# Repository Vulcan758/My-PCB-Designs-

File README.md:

# My-PCB-Designs-
all the designs I have so far

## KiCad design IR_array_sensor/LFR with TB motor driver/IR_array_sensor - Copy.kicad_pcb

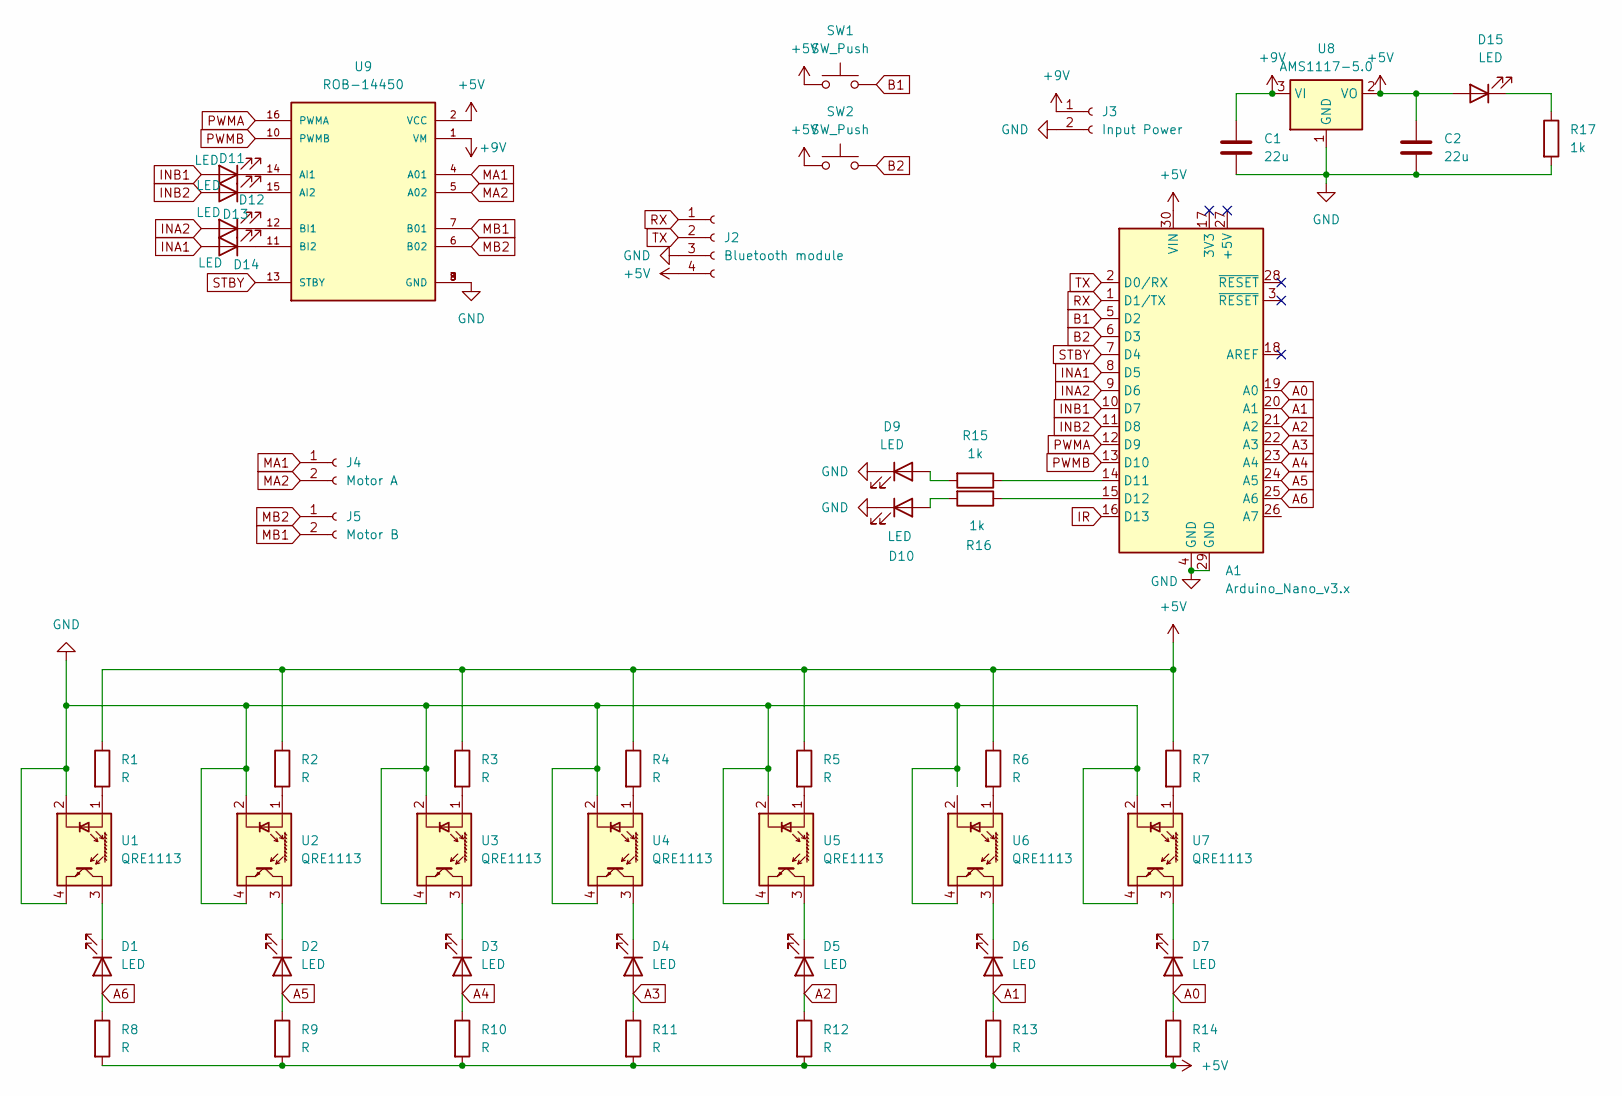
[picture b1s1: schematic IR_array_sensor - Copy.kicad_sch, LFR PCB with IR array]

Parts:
A1: Arduino_Nano_v3.x; Arduino_Nano
C1: 22u; CP_Radial_D5.0mm_P2.50mm
C2: 22u; CP_Radial_D5.0mm_P2.00mm
D1, D2, D3, D4, D5, D6, D7: LED; LED_D5.0mm
D9, D10, D11, D12, D13, D14, D15: LED; LED_D3.0mm
J2: Bluetooth module; PinSocket_1x04_P2.54mm_Vertical
J3: Input Power; BarrelJack_GCT_DCJ200-10-A_Horizontal
J4: Motor A; JST_XH_S2B-XH-A-1_1x02_P2.50mm_Horizontal
J5: Motor B; JST_XH_S2B-XH-A-1_1x02_P2.50mm_Horizontal
R1, R2, R3, R4, R5, R6, R7, R8, R9, R10, R11, R12, R13, R14: R; R_Axial_DIN0204_L3.6mm_D1.6mm_P5.08mm_Horizontal
R15, R16, R17: 1k; R_Axial_DIN0204_L3.6mm_D1.6mm_P5.08mm_Horizontal
SW1, SW2: SW_Push; SW_PUSH_6mm_H4.3mm
U1, U2, U3, U4, U5, U6, U7: QRE1113; OnSemi_CASE100AQ
U8: AMS1117-5.0; SOT-223-3_TabPin2
U9: ROB-14450; MODULE_ROB-14450; PARTREV 11-13-17

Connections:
+5V: A1.30 (VIN), C2.1, D15.2 (A), J2.4, R1.1, R2.1, R3.1, R4.1, R5.1, R6.1, R7.1, R8.2, R9.2, R10.2, R11.2, R12.2, R13.2, R14.2, SW1.1, SW2.1, U8.2 (VO), U9.2 (VCC)
+9V: C1.1, J3.1, U8.3 (VI), U9.1 (VM)
A0: A1.19 (A0), D7.2 (A), R14.1
A1: A1.20 (A1), D6.2 (A), R13.1
A2: A1.21 (A2), D5.2 (A), R12.1
A3: A1.22 (A3), D4.2 (A), R11.1
A4: A1.23 (A4), D3.2 (A), R10.1
A5: A1.24 (A5), D2.2 (A), R9.1
A6: A1.25 (A6), D1.2 (A), R8.1
B1: A1.5 (D2), SW1.2
B2: A1.6 (D3), SW2.2
GND: A1.4 (GND), A1.29 (GND), C1.2, C2.2, D9.1 (K), D10.1 (K), J2.3, J3.2, R17.2, U1.2 (K), U1.4, U2.2 (K), U2.4, U3.2 (K), U3.4, U4.2 (K), U4.4, U5.2 (K), U5.4, U6.4, U7.2 (K), U7.4, U8.1 (GND), U9.3 (GND), U9.8 (GND), U9.9 (GND)
INA1: A1.8 (D5), D14.2 (A)
INA2: A1.9 (D6), D13.2 (A)
INB1: A1.10 (D7), D11.2 (A)
INB2: A1.11 (D8), D12.2 (A)
IR: A1.16 (D13)
MA1: J4.1, U9.4 (A01)
MA2: J4.2, U9.5 (A02)
MB1: J5.2, U9.7 (B01)
MB2: J5.1, U9.6 (B02)
unnamed: A1.14 (D11), R15.1
unnamed: A1.15 (D12), R16.1
unnamed: D1.1 (K), U1.3
unnamed: D2.1 (K), U2.3
unnamed: D3.1 (K), U3.3
unnamed: D4.1 (K), U4.3
unnamed: D5.1 (K), U5.3
unnamed: D6.1 (K), U6.3
unnamed: D7.1 (K), U7.3
unnamed: D9.2 (A), R15.2
unnamed: D10.2 (A), R16.2
unnamed: D11.1 (K), U9.14 (AI1)
unnamed: D12.1 (K), U9.15 (AI2)
unnamed: D13.1 (K), U9.12 (BI1)
unnamed: D14.1 (K), U9.11 (BI2)
unnamed: D15.1 (K), R17.1
unnamed: R1.2, U1.1 (A)
unnamed: R2.2, U2.1 (A)
unnamed: R3.2, U3.1 (A)
unnamed: R4.2, U4.1 (A)
unnamed: R5.2, U5.1 (A)
unnamed: R6.2, U6.1 (A)
unnamed: R7.2, U7.1 (A)
PWMA: A1.12 (D9), U9.16 (PWMA)
PWMB: A1.13 (D10), U9.10 (PWMB)
RX: A1.1 (D1/TX), J2.1
STBY: A1.7 (D4), U9.13 (STBY)
TX: A1.2 (D0/RX), J2.2

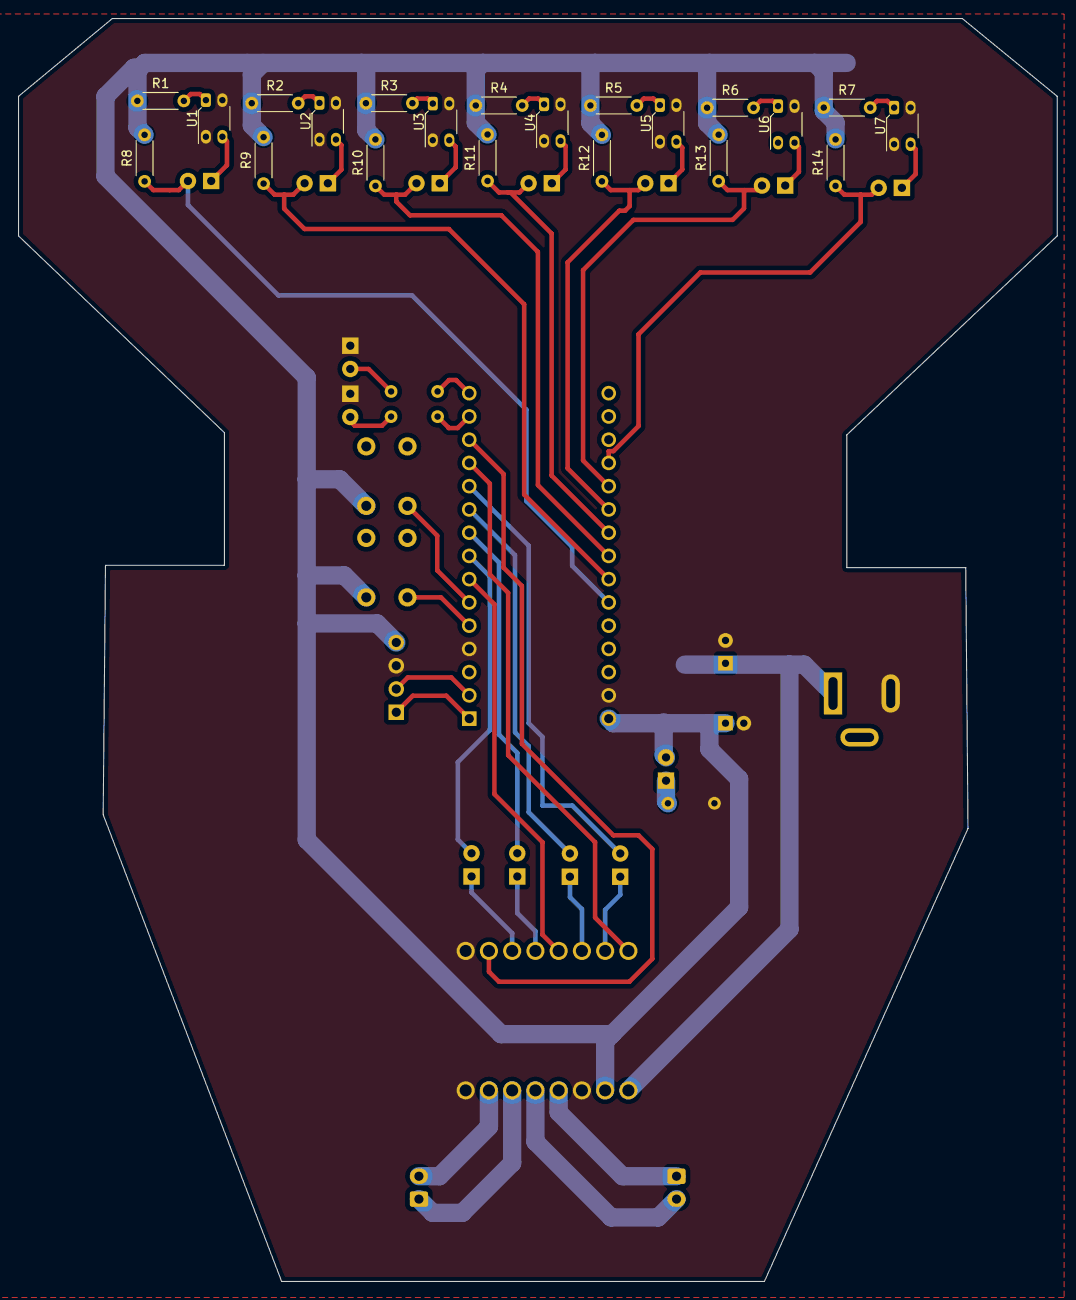
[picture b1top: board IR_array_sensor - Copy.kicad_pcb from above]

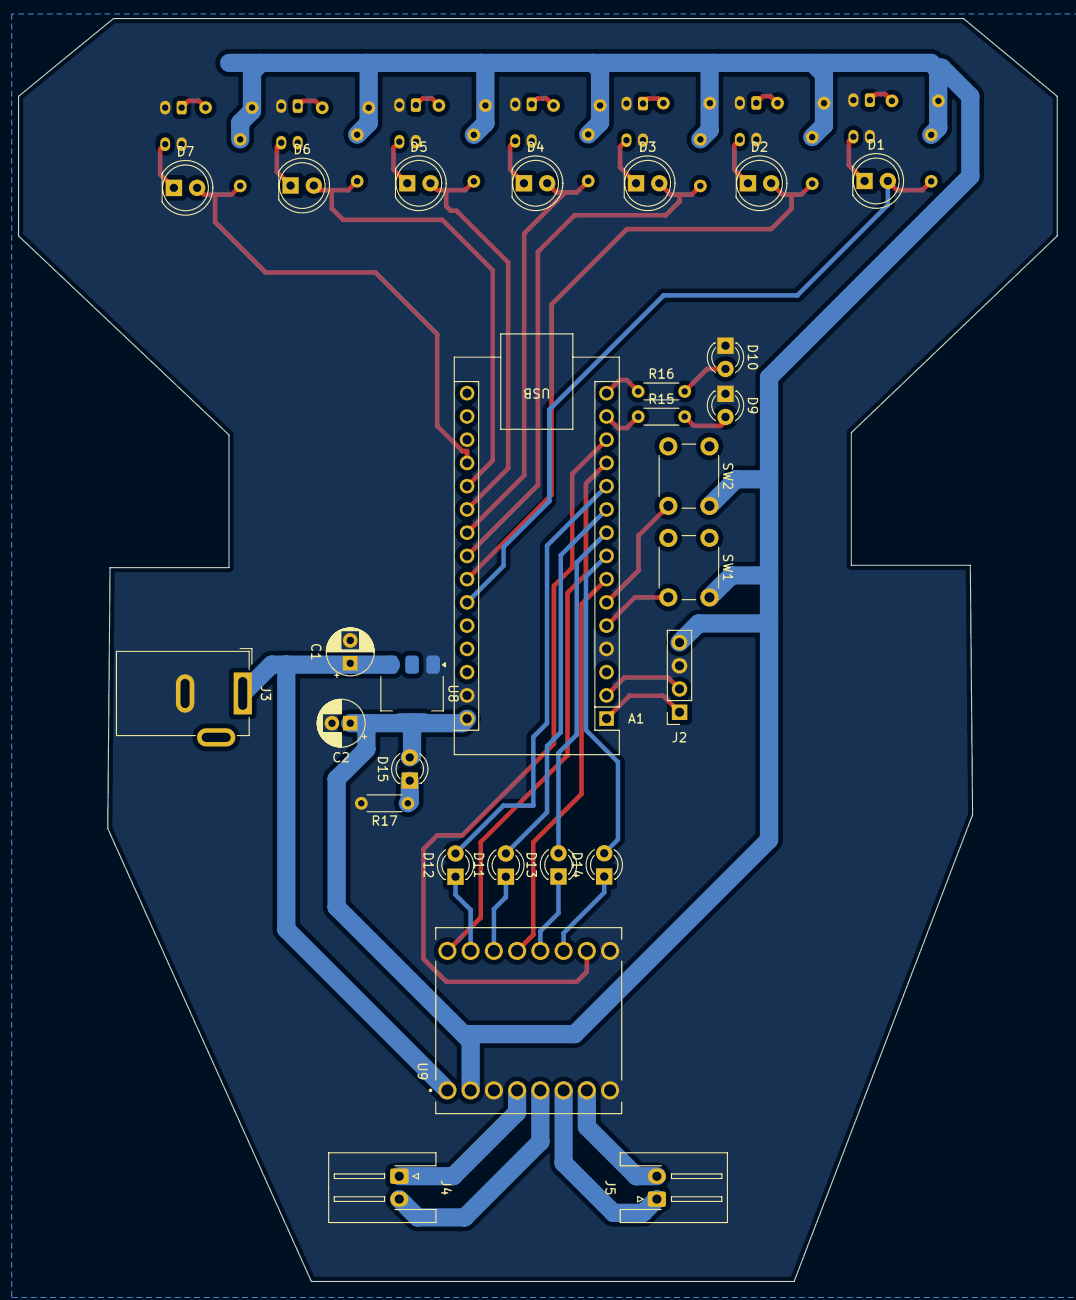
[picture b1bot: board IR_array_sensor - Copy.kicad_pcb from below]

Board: 2 copper layers, 113.5 x 138.0 mm, 49 parts (28 on the bottom side), 48 nets.

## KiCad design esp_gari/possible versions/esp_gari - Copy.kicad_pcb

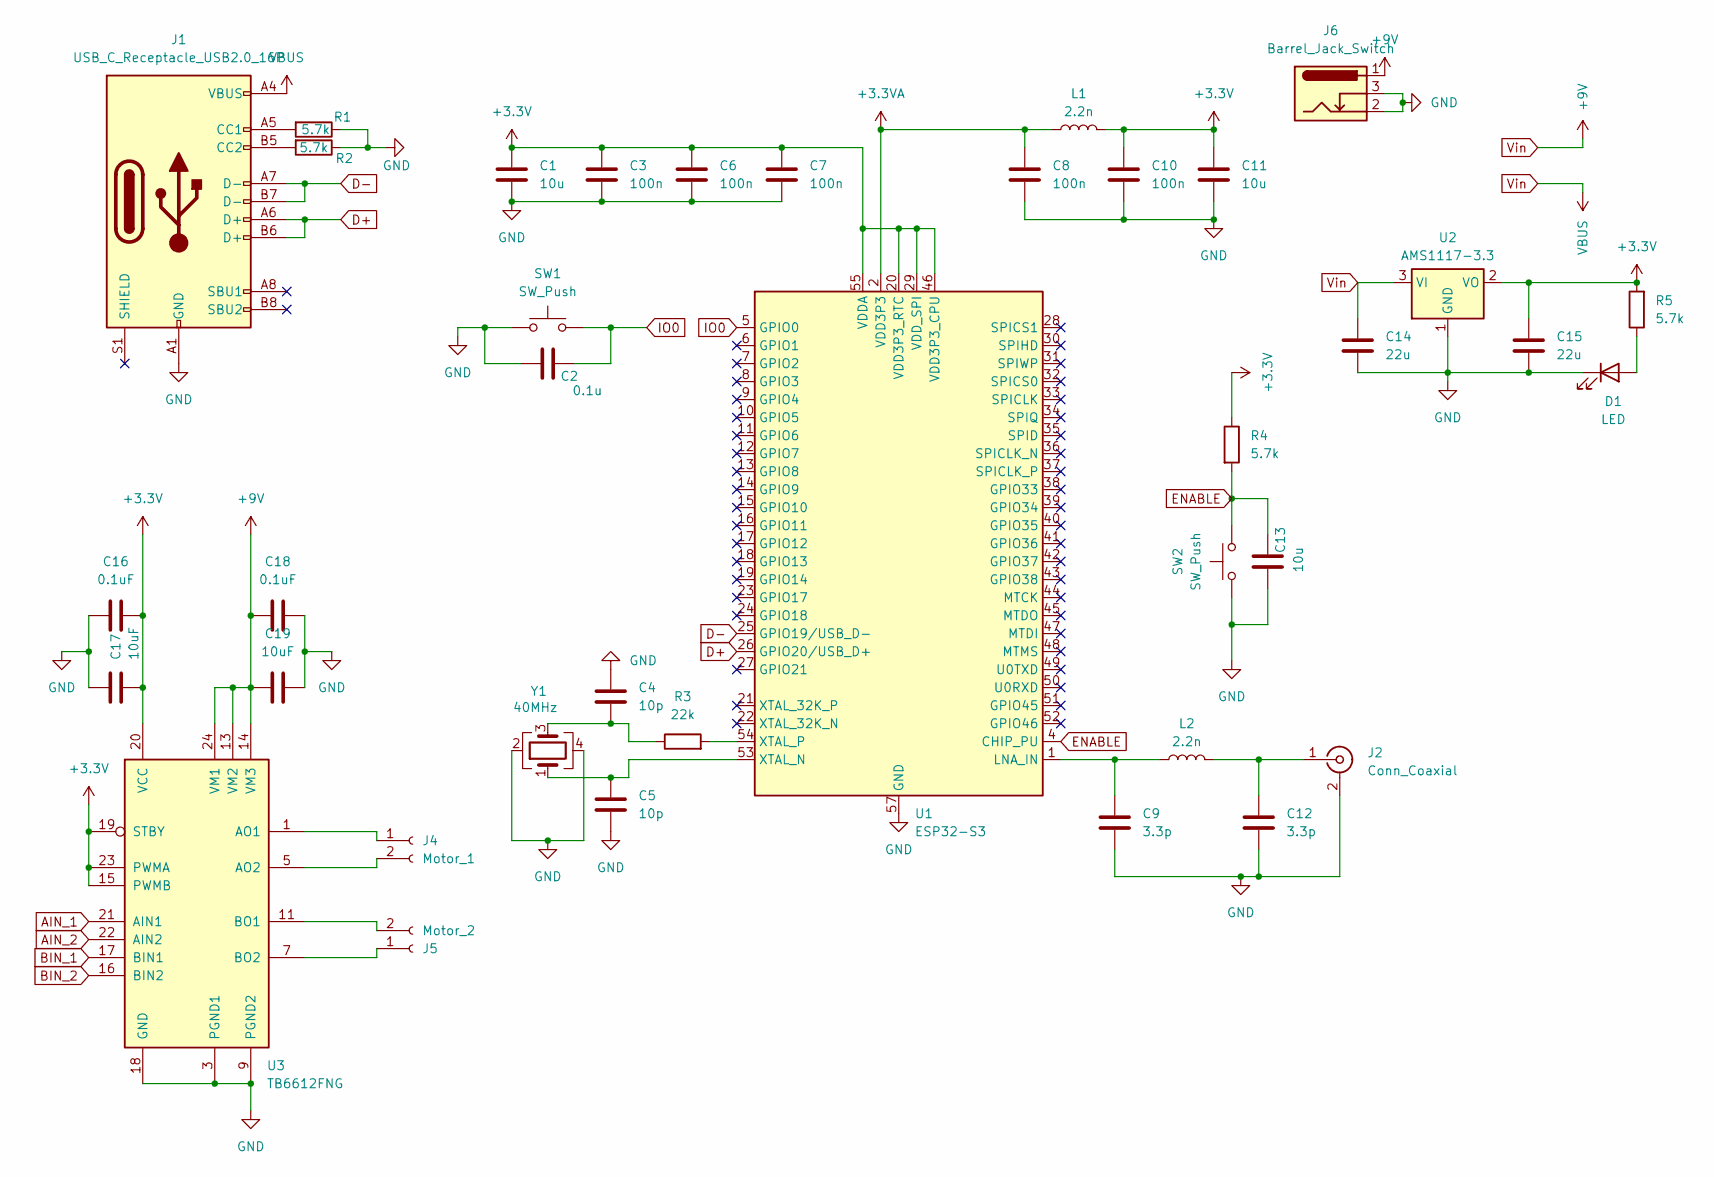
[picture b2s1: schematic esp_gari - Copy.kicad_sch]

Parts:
C1, C11, C13: 10u; C_0603_1608Metric
C2: 0.1u; C_0603_1608Metric
C3, C6, C7, C8, C10: 100n; C_0402_1005Metric
C4, C5: 10p; C_0603_1608Metric
C9, C12: 3.3p; C_0402_1005Metric
C14, C15: 22u; C_1210_3225Metric
C16, C18: 0.1uF; C_0603_1608Metric
C17, C19: 10uF; C_0603_1608Metric
D1: LED; LED_0805_2012Metric_Pad1.15x1.40mm_HandSolder
J1: USB_C_Receptacle_USB2.0_16P; USB_C_Receptacle_GCT_USB4105-xx-A_16P_TopMnt_Horizontal
J2: Conn_Coaxial; SMA_Molex_73251-1153_EdgeMount_Horizontal
J4: Motor_1; TerminalBlock_Phoenix_MPT-0,5-2-2.54_1x02_P2.54mm_Horizontal
J5: Motor_2; TerminalBlock_Phoenix_MPT-0,5-2-2.54_1x02_P2.54mm_Horizontal
J6: Barrel_Jack_Switch; BarrelJack_Horizontal
L1, L2: 2.2n; L_0402_1005Metric
R1, R2, R4, R5: 5.7k; R_0805_2012Metric
R3: 22k; R_0402_1005Metric
SW1, SW2: SW_Push; SW_SPST_B3U-1000P
U1: ESP32-S3; QFN-56-1EP_7x7mm_P0.4mm_EP4x4mm
U2: AMS1117-3.3; SOT-223-3_TabPin2
U3: TB6612FNG; SSOP-24_5.3x8.2mm_P0.65mm
Y1: 40MHz; Crystal_SMD_2520-4Pin_2.5x2.0mm

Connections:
+3.3V: C1.1, C3.1, C6.1, C7.1, C10.1, C11.1, C15.1, C16.2, C17.2, L1.2, R4.1, R5.2, U1.20 (VDD3P3_RTC), U1.29 (VDD_SPI), U1.46 (VDD3P3_CPU), U1.55 (VDDA), U1.56 (VDDA), U2.2 (VO), U3.15 (PWMB), U3.19 (STBY), U3.20 (VCC), U3.23 (PWMA)
+3.3VA: C8.1, L1.1, U1.2 (VDD3P3), U1.3 (VDD3P3)
AIN_1: U3.21 (AIN1)
AIN_2: U3.22 (AIN2)
BIN_1: U3.17 (BIN1)
BIN_2: U3.16 (BIN2)
D+: J1.A6 (D+), J1.B6 (D+), U1.26 (GPIO20/USB_D+)
D-: J1.A7 (D-), J1.B7 (D-), U1.25 (GPIO19/USB_D-)
ENABLE: C13.1, R4.2, SW2.2, U1.4 (CHIP_PU)
GND: C1.2, C2.2, C3.2, C4.1, C5.2, C6.2, C7.2, C8.2, C9.2, C10.2, C11.2, C12.2, C13.2, C14.2, C15.2, C16.1, C17.1, C18.2, C19.2, D1.1 (K), J1.A1 (GND), J1.A12 (GND), J1.B1 (GND), J1.B12 (GND), J2.2 (Ext), J6.2, J6.3, R1.1, R2.1, SW1.1, SW2.1, U1.57 (GND), U2.1 (GND), U3.3 (PGND1), U3.4 (PGND1), U3.9 (PGND2), U3.10 (PGND2), U3.18 (GND), Y1.2, Y1.4
IO0: C2.1, SW1.2, U1.5 (GPIO0)
unnamed: C4.2, R3.1, Y1.3
unnamed: D1.2 (A), R5.1
unnamed: J1.A5 (CC1), R1.2
unnamed: J1.B5 (CC2), R2.2
unnamed: C12.1, J2.1 (In), L2.2
unnamed: J4.1, U3.1 (AO1), U3.2 (AO1)
unnamed: J4.2, U3.5 (AO2), U3.6 (AO2)
unnamed: J5.1, U3.7 (BO2), U3.8 (BO2)
unnamed: J5.2, U3.11 (BO1), U3.12 (BO1)
unnamed: C9.1, L2.1, U1.1 (LNA_IN)
unnamed: C5.1, U1.53 (XTAL_N), Y1.1
unnamed: R3.2, U1.54 (XTAL_P)
Vin: C14.1, C18.1, C19.1, J1.A4 (VBUS), J1.A9 (VBUS), J1.B4 (VBUS), J1.B9 (VBUS), J6.1, U2.3 (VI), U3.13 (VM2), U3.14 (VM3), U3.24 (VM1)

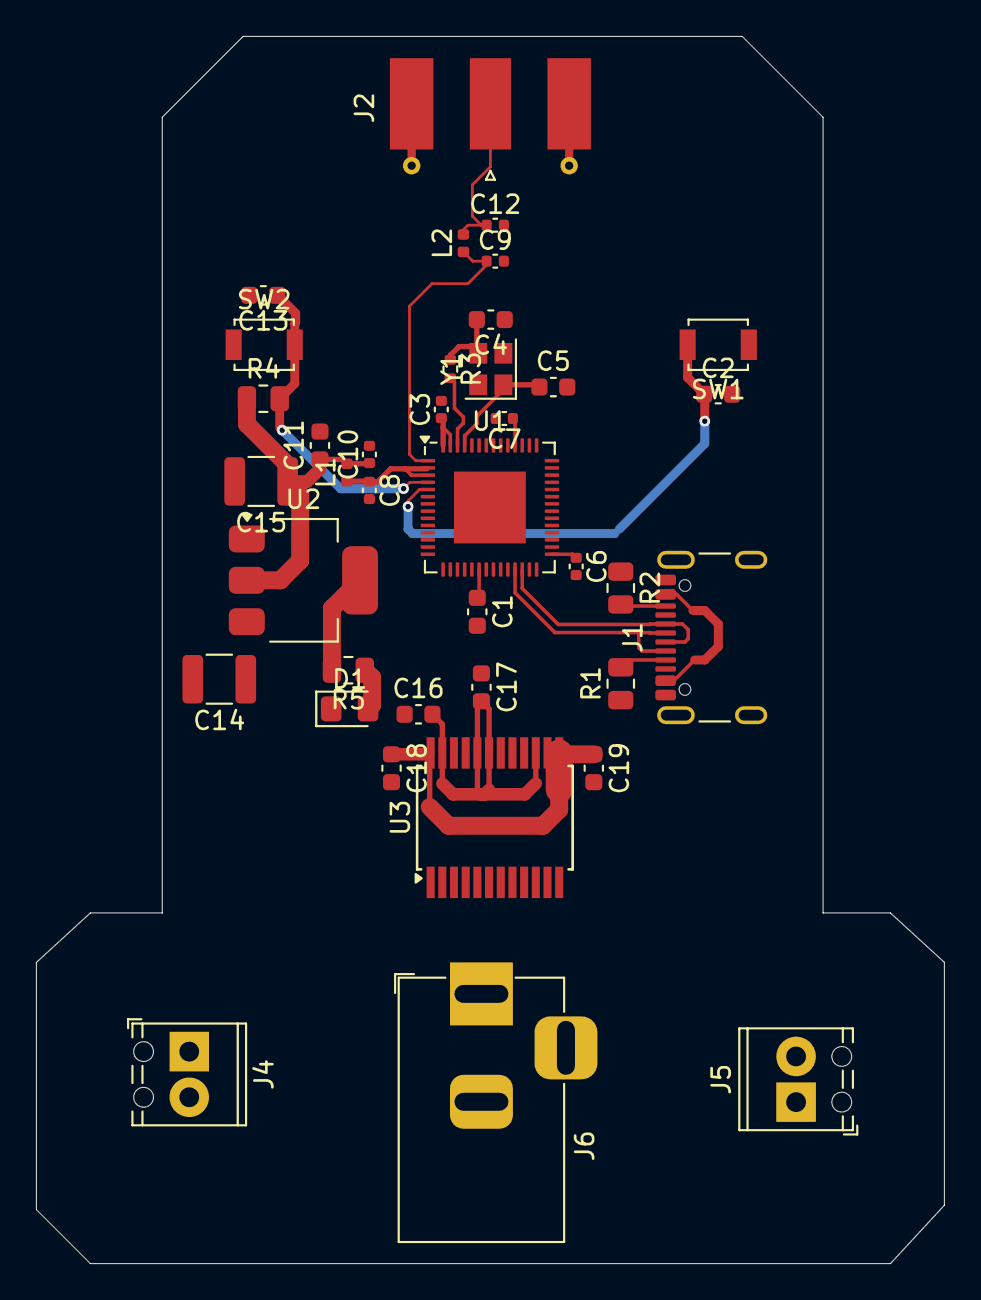
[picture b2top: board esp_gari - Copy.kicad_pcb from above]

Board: 4 copper layers, 50.5 x 68.2 mm, 38 parts (0 on the bottom side), 20 nets.
